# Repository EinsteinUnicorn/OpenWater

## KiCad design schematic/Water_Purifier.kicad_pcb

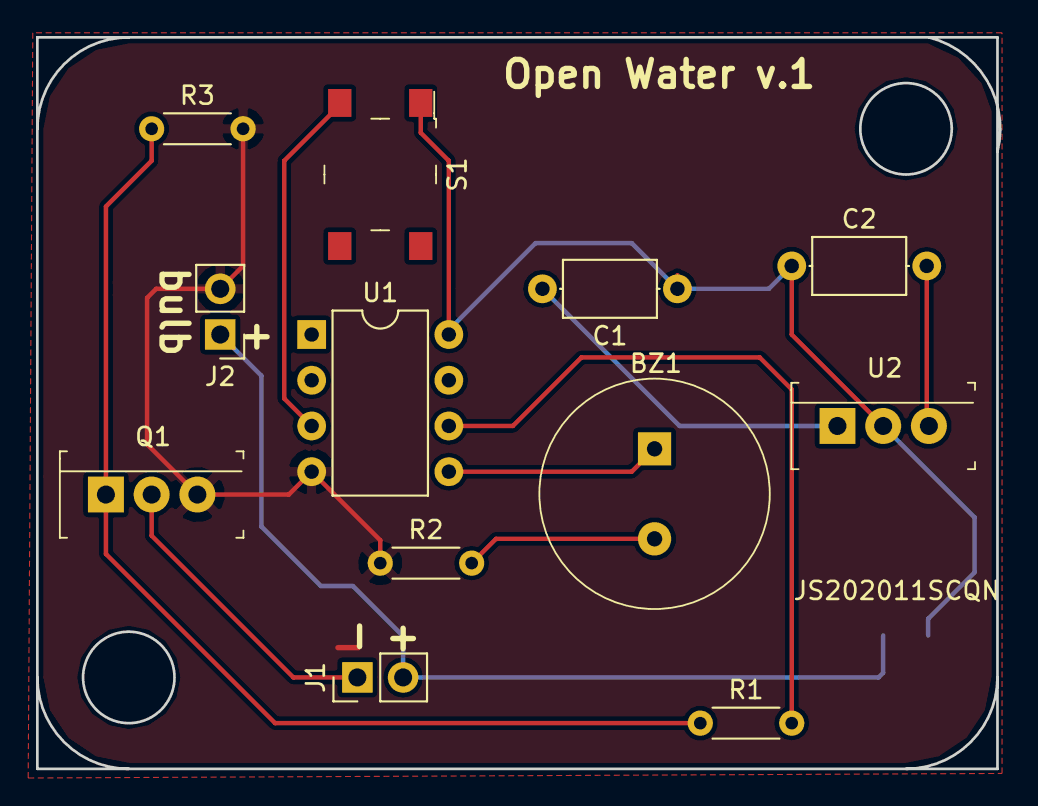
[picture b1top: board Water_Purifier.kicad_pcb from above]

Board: 2 copper layers, 53.5 x 40.6 mm, 13 parts (1 on the bottom side), 11 nets.

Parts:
BZ1: PS1240P02BT; Piezo_Transducer_THT_PS1240P02BT
C1, C2: C_Small; C_Axial_L5.1mm_D3.1mm_P7.50mm_Horizontal
J1, J2: Conn_01x02_Female; Socket_Strip_Straight_1x02_Pitch2.54mm
Q1: IRLB8721PBF; TO-220-3
R1, R2, R3: R; R_Axial_DIN0204_L3.6mm_D1.6mm_P5.08mm_Horizontal
S1: PTS645SM43SMTR92_LFS; Switch_Tactile_SMD_6x6mm_PTS645
S2: JS202011SCQN; Switch_Slide_JS202011SCQN
U1: ATTINY85-20PU; DIP-8_W7.62mm
U2: L7805CV; TO-220-3

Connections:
+9V: J1.2, J2.1, S2.5
GND: J2.2, Q1.3, R2.1, R3.2, U1.4
unnamed: BZ1.1, U1.5
unnamed: BZ1.2, R2.2
unnamed: C1.1, C2.1, S1.1, S2.6, U1.8, U2.2
unnamed: C1.2, U2.1
unnamed: C2.2, U2.3
unnamed: J1.1, Q1.2
unnamed: Q1.1, R1.1, R3.1
unnamed: R1.2, U1.6
unnamed: S1.3, U1.3

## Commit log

2018-10-13 added schematics, probably will change
    initial commint
2018-10-13 added initial code
2018-10-13 forgot to comment
2018-10-15 final version + gerbers
